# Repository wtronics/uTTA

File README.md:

# uTTA — The Micro ($\mu$) Thermal Transient Analyzer

## What's this TTA stuff anyhow?

Thermal Transient Analysis (TTA) is an advanced technique used to determine the thermal impedance model of a cooling path by measuring its thermal step response. This method is rigorously specified in the **JESD 51-14** standard and is brilliantly summarized in the following tutorials:
* [Transient thermal measurements and thermal equivalent circuit models](https://www.infineon.com/dgdl/Infineon-Thermal_equivalent_circuit_models-ApplicationNotes-v01_02-EN.pdf?fileId=db3a30431a5c32f2011aa65358394dd2) *(Highly recommended!)*
* [Structure function based evaluation of the thermal behavior of an LED](https://repository.tugraz.at/publications/1bz3b-q3w35) *(Definitely worth to read)*

Ideally, after completing a measurement, you should be able to transform the raw captured data into a thermal impedance ($Z_{th}$) curve—a staple graph found in almost every power semiconductor datasheet. In a nutshell, a $Z_{th}$ curve allows engineers to read the specific thermal resistance encountered by a device when a rectangular power pulse of a given duration $x$ is applied. By combining this thermal resistance with the dissipated power, you can calculate the exact junction temperature of the semiconductor at the end of that pulse. 

However, this math only holds true as long as the power pulse is brief enough not to hit the physical thermal boundaries of the semiconductor package itself. Once the heat propagates past those boundaries and into the rest of the assembly, you need a dedicated thermal impedance curve tailored to your specific, real-world cooling path. Nexperia published an excellent application note diving deeper into this topic: 
* [Nexperia AN11156](https://assets.nexperia.com/documents/application-note/AN11156.pdf)

Things get significantly more complicated when dealing with non-rectangular power pulses. While an "extended rectangular" approximation works for a rough estimate, it demands a massive amount of manual effort. Furthermore, if your ultimate goal is running a dynamic thermal simulation, static datasheet graphs are practically useless. For simulation purposes, the most elegant approach is to model the thermal cooling path using a network of RC circuits that mimic the system's heating and cooling behavior. Again, Nexperia offers a fantastic guide on how this is done: 
* [Nexperia AN11261](https://assets.nexperia.com/documents/application-note/AN11261.pdf)

But how do you actually extract these RC models for a specific power semiconductor combined with a custom heatsink? This is where the real headache begins. While you might occasionally find thermal models for a MOSFET, they are almost exclusively provided as encrypted SPICE models. Nexperia is one of the few refreshing exceptions, sometimes offering open thermal equivalent RC networks (structured as either Foster or Cauer models). But when it comes to the heatsink, manufacturers typically provide nothing more than a single, static thermal resistance value.

---

## How to perform these measurements?
### The Proper (and Expensive) Way
Capturing high-fidelity thermal transient measurements requires highly specialized hardware. The industry standard system is called **T3Ster**, originally engineered by MicReD (a Hungarian company later acquired by Siemens). 

Unsurprisingly, industrial equipment like this costs an absolute fortune—well into the high 5-to-6-figure Euro range. Because such professional tools are completely inaccessible for hobbyist or educational budgets, I set out to design and build my own miniature alternative.

### My own little Thermal Transient Analyzer (uTTA)
uTTA began as a passion project during the first COVID-19 lockdown. At the time, I was experimenting heavily with various power electronics (mostly MOSFET-based power switches and electronic loads) and kept running into the exact same wall: *How long can I dissipate a specific amount of surge power in this MOSFET before it reaches its critical destructive temperature?*

While several theoretical methods exist to solve this, every single one of them requires you to know the exact thermal impedance curve of your unique mechanical setup.

#### Target Picture
The following checklist outlines the core objectives of this project and what has been successfully accomplished so far:
* [x] **Measurement Hardware:** Design a hardware platform capable of performing single-channel thermal impedance measurements while simultaneously monitoring at least 2 additional channels for future thermal coupling analysis.
* [x] **Postprocessing Software:** Build a software toolkit to process raw measurement data and extract clean thermal impedance ($Z_{th}$) curves.
* [x] **Thermal Coupling:** Add software/hardware support to measure thermal coupling between adjacent semiconductors.
* [x] **Self-Calibration:** Implement software utilities to calibrate the internal measurement hardware.
* [ ] **Time Constant Spectra:** Implement the ability to calculate the time constant spectrum of the $Z_{th}$ curve via the NID (Network Identification by Deconvolution) method (utilizing either classical FFT deconvolution or a Bayesian approach).
* [ ] **RC Model Extraction:** Automatically extract equivalent RC thermal networks directly from the calculated time constant spectrum.
* [x] **Junction Calibration:** Develop software and hardware tools to calibrate the temperature coefficient of the junction under test.
* [ ] **Hardware Simulator:** Build a dedicated hardware simulator capable of generating highly predictable and repeatable cooling curves to rigorously validate all subsequent software processing steps.

#### Design Requirements
The device must adhere to the following constraints:
* **User-Friendly:** It should be straightforward and intuitive to operate.
* **Cost-Effective:** Extremely cheap and easy to replicate. Target budget: **€150** covering all components and the PCB.
* **Highly Available:** Rely exclusively on off-the-shelf components; absolutely no hard-to-find or "unobtanium" parts.
* **High-Current Handling:** Integrate an onboard heating current switch rated for up to 15A DC which could be upgraded to even higher heating currents.
* **Auxiliary Sensing:** Include a few Type-K thermocouple interfaces for low-speed ambient/heatsink monitoring (< 5 Samples/s).
* **Multi-Junction Tracking:** Capable of measuring the primary Junction Under Test (JUT) alongside 2 secondary monitoring junctions to evaluate thermal coupling.
* **Dynamic Range Optimization:** Provide software-selectable gain settings for the JUT monitor to maximize ADC resolution throughout the transient event.
* **High-Speed Sampling Speed:** Deliver an ultra-fast sampling rate of at least 1MS/s immediately following the deactivation of the heating current to capture the critical early transient behavior.
* **Intelligent Data Reduction:** Automatically taper down the sampling rate as the transient slows down, preventing the accumulation of massive, redundant data logs.
* **Onboard Storage:** Buffer all high-speed data directly to built-in local memory.
* **PC Control:** Managed entirely via a clean, accessible PC graphical user interface (GUI).

---

# The Implementation

## µTTA Hardware
This is the current physical state of the µTTA hardware. The architecture utilizes a compact 3-layer PCB stack enclosed in a custom 3D-printed housing. The design files for the mechanical housing are available under `010_Hardware/060_Mechanics`.

## The Final Test Setup (Simplified)
Below is an overview of the active test setup. The JUT assembly is positioned right next to the power supply. 

> **Note on Environment:** In a professional testing environment, the JUT assembly must be enclosed in a "still air chamber" to isolate the measurement from volatile ambient drafts. Ideally, the device would be mounted onto a temperature-controlled cold plate, but that represents an unnecessary layer of complexity for the scope of this hobby project.

The system is composed of the following core blocks:

### The Heating Power Supply
This unit drives the raw heating current through the Junction Under Test (JUT). While I happen to use a massive 40A bench supply in my lab, any standard power supply featuring an adjustable current limit up to 10A is perfectly adequate for most scenarios. 

The exact current required depends heavily on the specific junction properties and the thermal resistance of the cooling assembly under evaluation. If you are targeting a high-power device with ultra-low thermal resistance (e.g., < 10 K/W), a meatier power supply becomes necessary to force a measurable temperature delta. The supply voltage itself is uncritical; in my configurations, I typically set it to roughly 3V, which provides plenty of headroom to comfortably drive the required current.

### The Junction Under Test
*(To be continued...)*

---

## The JUT Setup

Lacking access to a formal industrial application board I can show in public, I assembled a custom test fixture that closely mimics real-world conditions. The setup consists of three spare MOSFETs bolted to a shared aluminum heatsink. 
The transistors are electrically isolated from the heatsink using standard mica ("glimmer") washers and silicone thermal pads. However, to establish a shared return path for the sense current across all monitored devices, the isolating washers on the mounting screws were intentionally omitted to bridge the drains of all three MOSFETs together. The Gate and Source pins of each individual MOSFET are shorted to prevent spurious turn-on events triggered by static charges. 
Furthermore, each MOSFET is routed through a dedicated coaxial sense cable to accurately monitor the forward voltage drop of the internal body diodes and supply the delicate measurement current. The primary heated junction is also hooked up to heavy-gauge wires to carry the high heating current. These low-inductance lines are custom-made by braiding high-frequency (HF) litz wire. To minimize the overall loop area and shield against inductive voltage spikes, the positive and negative current paths are tightly bundled inside a braided insulating sleeve.

# ToDo
- [x] Build calibration GUI for uTTA hardware.
- [x] Build calibration GUI for DUT scaling factors.
- [x] Document ST Nucleo-Board jumper configurations.
- [ ] Get the mathematical deconvolution algorithm fully operational.
- [ ] Implement automatic RC-model calculation from the time constant spectrum.
- [ ] Develop a modern, native standalone GUI (moving away from LabVIEW).
- [ ] Overhaul and expand the general documentation.

# Possible Improvements for Future Designs
- [ ] Implement finer gain steps for low-level diode voltage measurements.
- [x] Integrate software-controlled offset adjustment via an onboard DAC.
- [x] Integrate software-adjustable measurement current sources (e.g., DAC-controlled Enhanced Howland Current Sources).
- [ ] Migrate away from the ST Nucleo breakout ecosystem in favor of a fully custom, integrated PCB design. *(Benefits: Eliminates bulky stack-up connectors, drastically improves high-speed signal integrity, allows a highly stable dedicated ADC voltage reference, and enables a native onboard USB interface bypassing the ST-Link debugger).*

## Design Choices

Let's be candid: this system is far from a flawless commercial product. As stated at the beginning, this started as a quick-and-dirty quarantine project during the COVID-19 pandemic. I never anticipated that I would still be actively evolving it over 6 years later. The subject matter completely hooked me, though personal commitments have limited the amount of focused time I can dedicate to it. Because both the hardware and software architectures have undergone iterative overhauls, some design choices might appear slightly unorthodox to an outside observer. Here is the underlying engineering rationale:

* **Why store measurement data in local flash memory instead of streaming it directly to a PC over a serial interface?**
  * Our serial connection maxes out at 250 kBaud, which is fundamentally incapable of sustaining the throughput required during the initial 1 MS/s ultra-fast sampling window. Additionally, the microcontroller lacks the RAM capacity required to buffer the millions of high-speed points simultaneously before a delayed dump. Therefore, high-speed hardware-level buffering to external non-volatile storage was mandatory. While I initially used a micro SD card running FATfs, the aggressive write cycles quickly destroyed the cards. Upgrading to a robust NOR Flash chip running **littleFS** completely solved this reliability bottleneck.

* **Why is there only one switchable amplifier? Shouldn't every tracking channel have its own dynamic gain stage?**
  * The switchable programmable gain amplifier (PGA) is intentionally reserved for the primary heated channel. When the massive heating current passes through the JUT, its forward voltage is substantially larger due to the internal resistance. The amplifier must dynamically drop its gain down during this phase to prevent clipping and keep the signal within the measurable ADC window. 
  * The secondary channels, by contrast, are strictly passive—they monitor adjacent unheated diodes utilizing a constant, low-level measurement current where no severe voltage swings occur. A fixed gain stage is perfectly sufficient to map standard silicon diodes or MOSFET body diodes across these monitoring channels.

* **Why did you build the original GUI in LabVIEW?**
  * Frankly, because I use it daily in my day job as a self-proclaimed "lazy" senior hardware developer! 😉 In industrial prototyping, test software needs to be deployed rapidly, and that is precisely where LabVIEW excels. 
  * I am well aware that LabVIEW is quite polarizing in the developer community, but for whipping together a functional, interactive GUI without getting bogged down in TKinter or basic UI positioning math, it remains an incredibly fast tool.
  * **Update (July 1, 2026):** The complete postprocessing toolchain has now been successfully migrated to a modern Python ecosystem utilizing `TTKbootstrap`. Consequently, I am officially working on sunsetting the legacy LabVIEW GUI in upcoming releases. The foundational groundwork was recently completed following the development of our native SCPI driver for the uTTA hardware.

* **Why power the gate driver of the high-current heating switch with an external battery instead of a standard bench supply?**
  * In the early prototyping phases, I did use a secondary isolated bench supply to power the gate drive circuitry. However, I found myself locked in an endless, frustrating battle with nasty common-mode noise issues during high-current switching events. Swapping that power rail over to a completely floating 9V/12V battery completely severed the noise path and instantly wiped out all common-mode artifacts.

---

# A Note on AI

Given how pervasive AI has become in modern software development, I wanted to include a brief, transparent disclosure regarding its role in this repository. This project leverages generative AI to accelerate development velocities and explore alternative conceptual approaches. 

To be clear: the core firmware running on the microcontroller is entirely handwritten from scratch. On the host PC side, things are a bit more collaborative. I heavily utilize AI to spin up structural boilerplate, generate templates, and prototype abstract UI concepts. For instance, the clean HTML layout used to compile the final measurement reports was largely authored by AI, as LLMs are remarkably proficient at building attractive front-end layouts. 

That being said, every single line of code or structural layout spat out by an AI is meticulously peer-reviewed by a human before merging. AI tools are notoriously confident when generating bugs; for example, LLMs absolutely love using deprecated syntax or obsolete methods from older versions of `tkinter` and `TTKbootstrap`. Treat it as a highly capable but slightly reckless assistant!

P.S.: This reame was also redacted by AI :).

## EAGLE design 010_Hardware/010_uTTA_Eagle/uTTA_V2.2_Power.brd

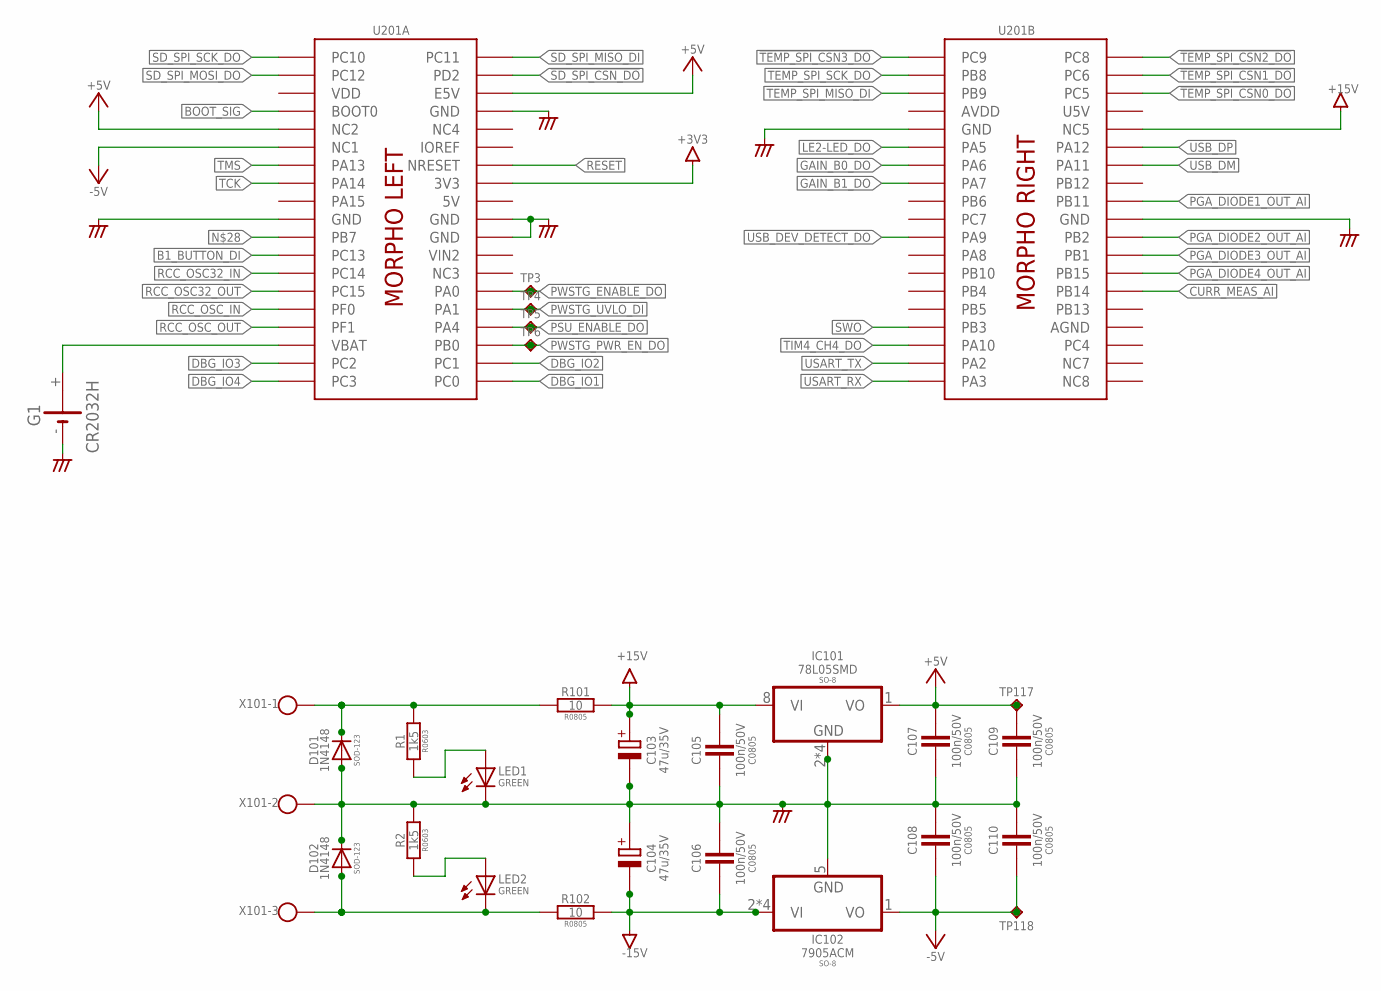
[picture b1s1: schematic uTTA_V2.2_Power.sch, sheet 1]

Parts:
C103, C104: 47u/35V; PANASONIC_D
C105, C106, C107, C108, C109, C110: 100n/50V; C0805
D101, D102: 1N4148; SOD123
G1: CR2032H
IC101: 78L05SMD; SO08
IC102: 7905ACM; SO08
LED1, LED2: GREEN; SML0805
R1, R2: 1k5; R0603
R101, R102: 10; R0805
TP3, TP4, TP5, TP6, TP117, TP118: TPC90H30; C90H30
U201: NUCLEO_F103_BOT; NUCLEO_BRD64_LOWER
X101: AST_03_3,5MM; AST_453_3,5

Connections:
5V: U201.L_5V (5V)
!SD_SPI_CSN_DO: U201.L_PD2 (PD2)
!TEMP_SPI_CSN0_DO: U201.R_PC5 (PC5)
!TEMP_SPI_CSN1_DO: U201.R_PC6 (PC6)
!TEMP_SPI_CSN2_DO: U201.R_PC8 (PC8)
!TEMP_SPI_CSN3_DO: U201.R_PC9 (PC9)
+3V3: U201.L_3V3 (3V3)
+5V: C107.1, C109.1, IC101.1 (VO), TP117.P$1, U201.L_E5V (E5V), U201.L_NC2 (NC2); also elsewhere on the board
+15V: C103.+, C105.1, IC101.8 (VI), R101.2, U201.R_NC5 (NC5)
-5V: C108.2, C110.2, IC102.1 (VO), TP118.P$1, U201.L_NC1 (NC1); also elsewhere on the board
-15V: C104.-, C106.2, IC102.2 (VI), IC102.3 (VI), IC102.6 (VI), IC102.7 (VI), R102.2
AGND: C103.-, C104.+, C105.2, C106.1, C107.2, C108.1, C109.2, C110.1, D101.A, D102.C, G1.-, IC101.2 (GND), IC101.3 (GND), IC101.6 (GND), IC101.7 (GND), IC102.5 (GND), LED1.C, R2.1, U201.L_GND (GND), U201.L_GND3 (GND), U201.L_GND4 (GND), U201.L_GND5 (GND), U201.R_AGND (AGND), U201.R_GND7 (GND), U201.R_GND8 (GND), X101.2_1, X101.2_2; also elsewhere on the board
AVDD: U201.R_AVDD (AVDD)
B1_BUTTON_DI: U201.L_PC13 (PC13)
BOOT_SIG: U201.L_BOOT0 (BOOT0)
CURR_MEAS_AI: U201.R_PB14 (PB14); also elsewhere on the board
DBG_IO1: U201.L_PC0 (PC0)
DBG_IO2: U201.L_PC1 (PC1)
DBG_IO3: U201.L_PC2 (PC2)
DBG_IO4: U201.L_PC3 (PC3)
GAIN_B0_DO: U201.R_PA6 (PA6)
GAIN_B1_DO: U201.R_PA7 (PA7)
IN+: D101.C, R1.1, R101.1, X101.1_1, X101.1_2
IN-: D102.A, LED2.C, R102.1, X101.3_1, X101.3_2
LE2-LED_DO: U201.R_PA5 (PA5)
unnamed: G1.+, U201.L_VBAT (VBAT)
unnamed: LED1.A, R1.2
unnamed: LED2.A, R2.2
PGA_DIODE1_OUT_AI: U201.R_PB11 (PB11)
PGA_DIODE2_OUT_AI: U201.R_PB2 (PB2)
PGA_DIODE3_OUT_AI: U201.R_PB1 (PB1)
PGA_DIODE4_OUT_AI: U201.R_PB15 (PB15)
PSU_ENABLE_DO: TP5.P$1, U201.L_PA4 (PA4); also elsewhere on the board
PWSTG_ENABLE_DO: TP3.P$1, U201.L_PA0 (PA0); also elsewhere on the board
PWSTG_PWR_EN_DO: TP6.P$1, U201.L_PB0 (PB0); also elsewhere on the board
PWSTG_UVLO_DI: TP4.P$1, U201.L_PA1 (PA1); also elsewhere on the board
RCC_OSC32_IN: U201.L_PC14 (PC14)
RCC_OSC32_OUT: U201.L_PC15 (PC15)
RCC_OSC_IN: U201.L_PF0 (PF0)
RCC_OSC_OUT: U201.L_PF1 (PF1)
RESET: U201.L_RESET (NRESET)
SD_SPI_MISO_DI: U201.L_PC11 (PC11)
SD_SPI_MOSI_DO: U201.L_PC12 (PC12)
SD_SPI_SCK_DO: U201.L_PC10 (PC10)
SWO: U201.R_PB3 (PB3)
TCK: U201.L_PA14 (PA14)
TEMP_SPI_MISO_DI: U201.R_PB9 (PB9)
TEMP_SPI_SCK_DO: U201.R_PB8 (PB8)
TIM4_CH4_DO: U201.R_PA10 (PA10)
TMS: U201.L_PA13 (PA13)
U5V: U201.R_U5V (U5V)
USART_RX: U201.R_PA3 (PA3)
USART_TX: U201.R_PA2 (PA2)
USB_DEV_DETECT_DO: U201.R_PA9 (PA9)
USB_DM: U201.R_PA11 (PA11)
USB_DP: U201.R_PA12 (PA12)
VDD: U201.L_VDD (VDD)
VIN2: U201.L_VIN (VIN2)

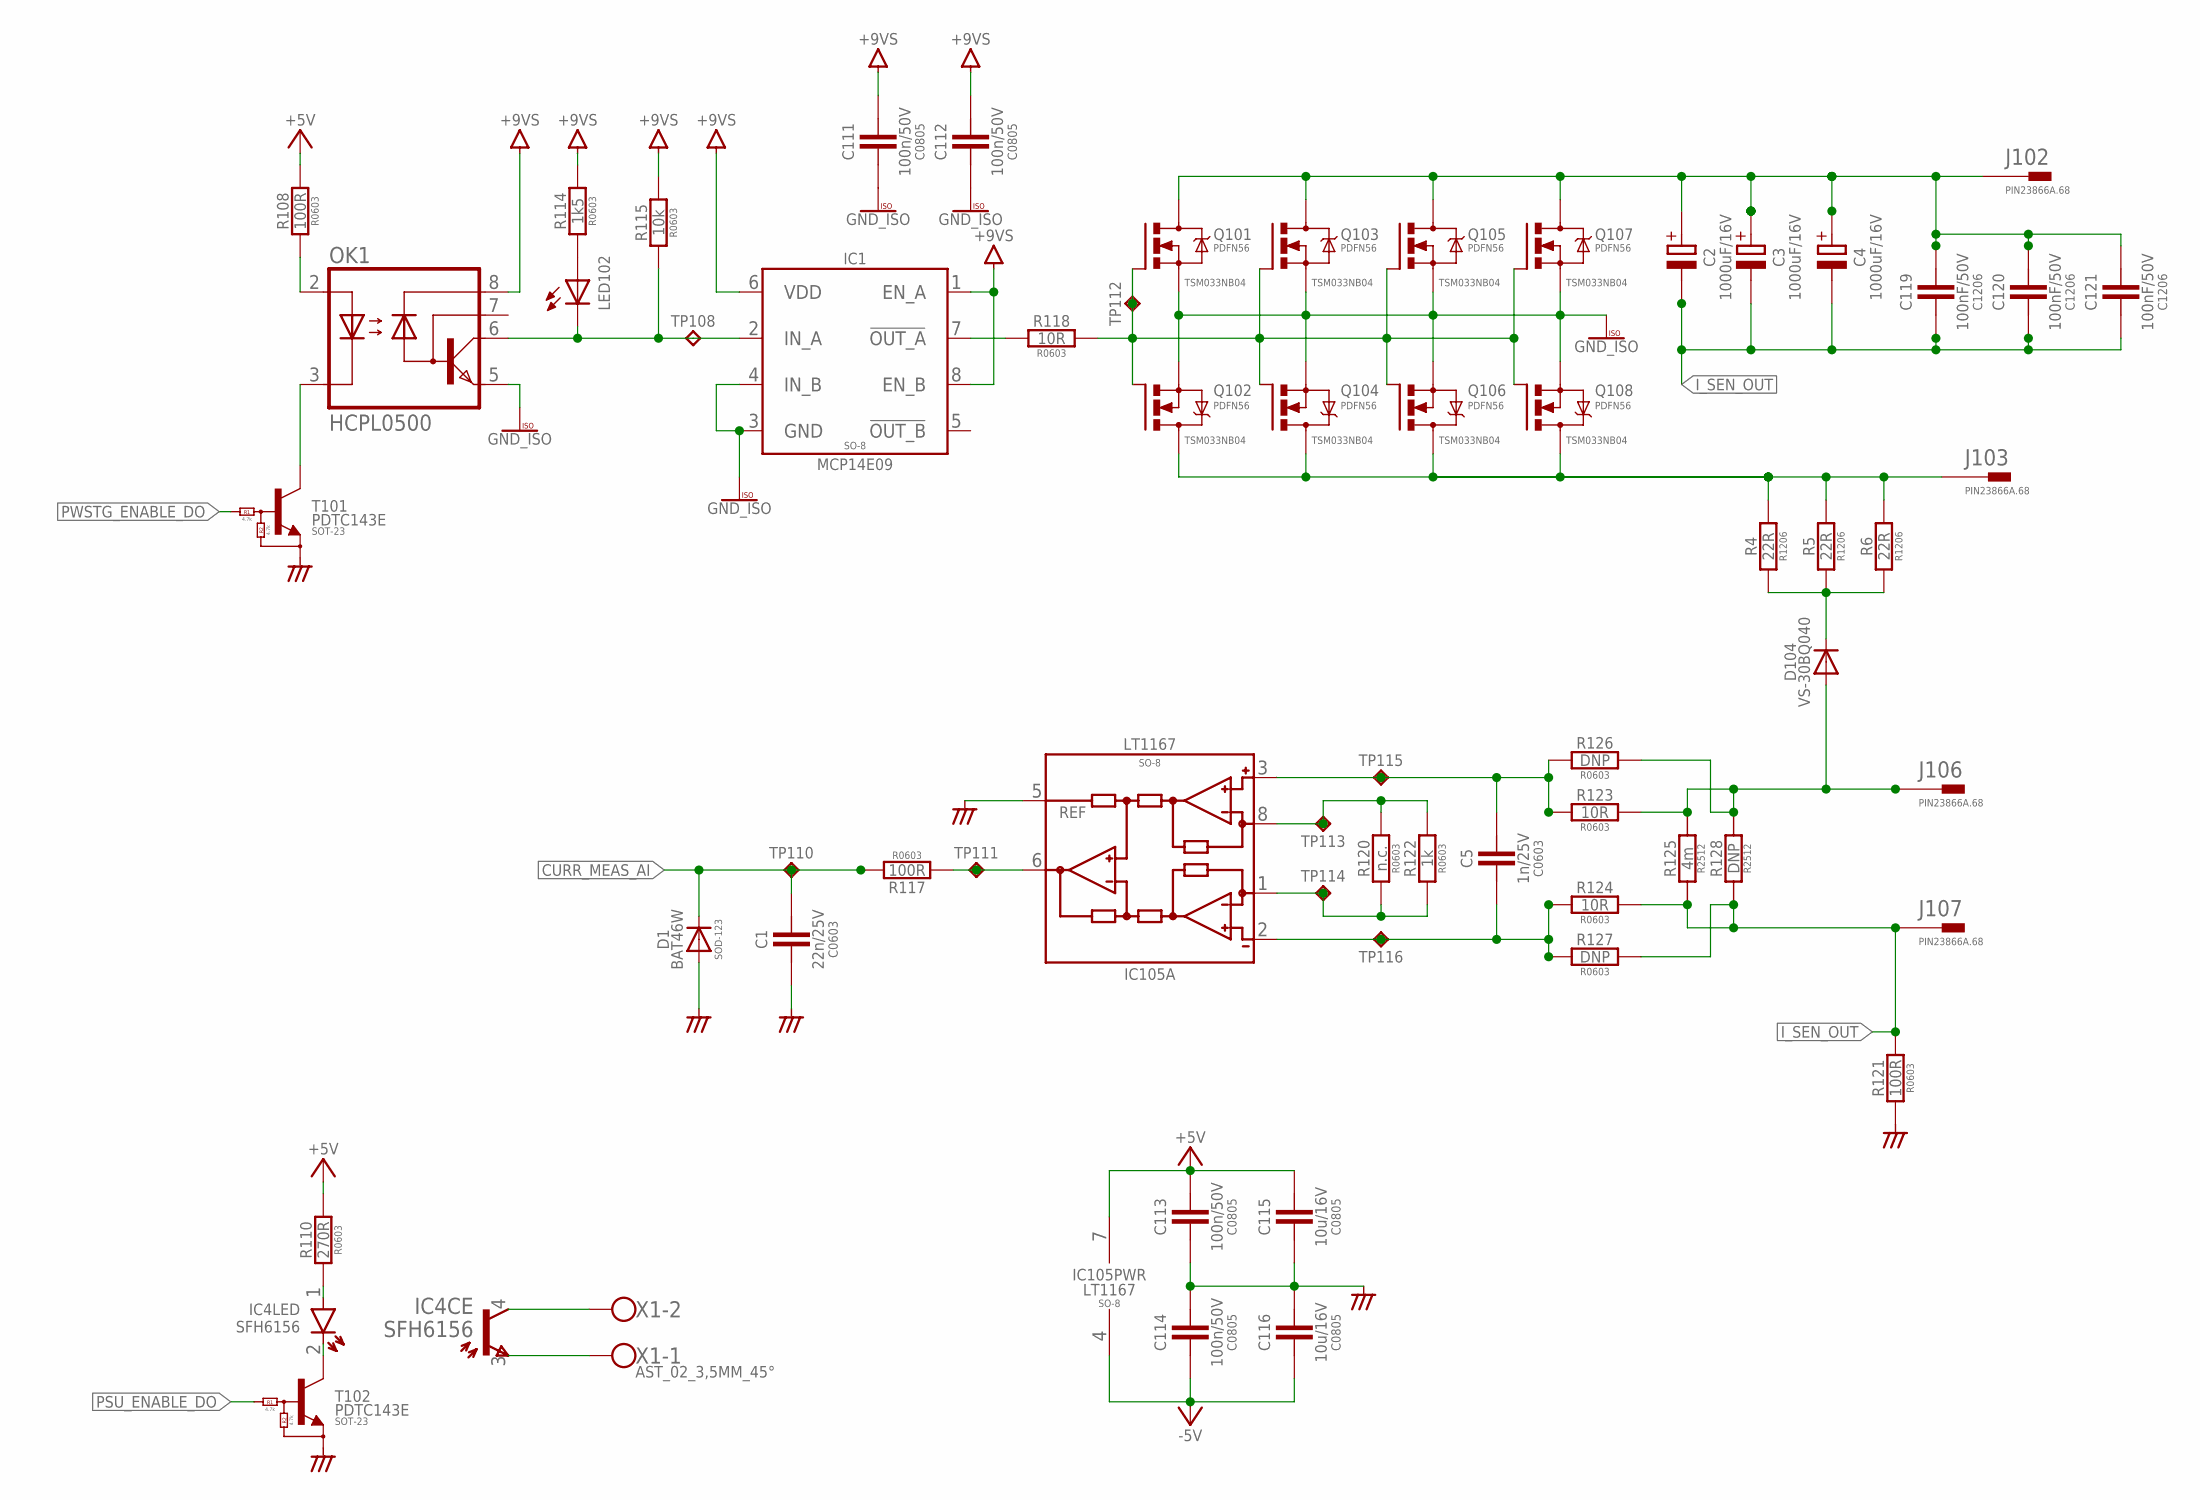
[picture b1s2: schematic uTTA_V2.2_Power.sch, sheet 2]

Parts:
C1: 22n/25V; C0603
C2, C3, C4: 1000uF/16V; E5-10,5
C5: 1n/25V; C0603
C111, C112, C113, C114: 100n/50V; C0805
C115, C116: 10u/16V; C0805
C119, C120, C121: 100nF/50V; C1206
D1: BAT46W; SOD123
D104: VS-30BQ040; SMC
IC1: MCP14E09; SO-08
IC4: SFH6156; SFH; MPN SFH6156-4T
IC105: LT1167; SO08
J102, J103, J106, J107: PIN23866A.68; VOGT_3866A.68
LED102: LEDSML0805; SML0805
OK1: HCPL0500; SOIC08
Q101, Q102, Q103, Q104, Q105, Q106, Q107, Q108: TSM033NB04; PDFN56
R4, R5, R6: 22R; R1206
R108, R117, R121: 100R; R0603
R110: 270R; R0603
R114: 1k5; R0603
R115: 10k; R0603
R118, R123, R124: 10R; R0603
R120: n.c.; R0603
R122: 1k; R0603
R125: 4m; R2512
R126, R127: DNP; R0603
R128: DNP; R2512
T101, T102: PDTC143E; SOT23
TP108, TP110, TP111, TP112, TP115, TP116: TPC90H30; C90H30
TP113, TP114: TP; C90
X1: AST_02_3,5MM_45°; AST_452_3,5

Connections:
9V_SWITCHED: C111.1, C112.1, IC1.1 (EN_A), IC1.6 (VDD), IC1.8 (EN_B), OK1.8 (VCC), R114.1, R115.1; also elsewhere on the board
+5V: C113.1, C115.1, IC105.7 (V+), R108.1, R110.1; also elsewhere on the board
-5V: C114.2, C116.2, IC105.4 (V-); also elsewhere on the board
AGND: C1.2, C113.2, C114.1, C115.2, C116.1, D1.A, IC105.5 (REF), R121.1, T101.2 (E), T102.2 (E); also elsewhere on the board
CURR_AMP_GAIN_N: IC105.1 (RG), R120.1, R122.1, TP114.P$1
CURR_AMP_GAIN_P: IC105.8 (RG), R120.2, R122.2, TP113.P$1
CURR_AMP_OUT: IC105.6 (OUT), R117.2, TP111.P$1
CURR_MEAS_AI: C1.1, D1.C, R117.1, TP110.P$1; also elsewhere on the board
GND_ISO: C111.2, C112.2, IC1.3 (GND), IC1.4 (IN_B), OK1.5 (GND), Q101.P$1 (S), Q101.P$2 (S), Q101.P$3 (S), Q102.P$1 (S), Q102.P$2 (S), Q102.P$3 (S), Q103.P$1 (S), Q103.P$2 (S), Q103.P$3 (S), Q104.P$1 (S), Q104.P$2 (S), Q104.P$3 (S), Q105.P$1 (S), Q105.P$2 (S), Q105.P$3 (S), Q106.P$1 (S), Q106.P$2 (S), Q106.P$3 (S), Q107.P$1 (S), Q107.P$2 (S), Q107.P$3 (S), Q108.P$1 (S), Q108.P$2 (S), Q108.P$3 (S); also elsewhere on the board
I_SENSE_N: C5.2, IC105.2 (-IN), R124.2, R127.2, TP116.P$1
I_SENSE_P: C5.1, IC105.3 (+IN), R123.1, R126.1, TP115.P$1
I_SEN_IN: D104.A, J106.A1, J106.A2, R123.2, R125.2 (B), R126.2, R128.2 (B)
I_SEN_OUT: C2.-, C3.-, C4.-, C119.2, C120.2, C121.2, J107.A1, J107.A2, R121.2, R124.1, R125.1 (A), R127.1, R128.1 (A)
unnamed: C2.+, C3.+, C4.+, C119.1, C120.1, C121.1, J102.A1, J102.A2, Q101.P$5 (D), Q101.P$6 (D), Q101.P$7 (D), Q101.P$8 (D), Q101.P$9 (D), Q103.P$5 (D), Q103.P$6 (D), Q103.P$7 (D), Q103.P$8 (D), Q103.P$9 (D), Q105.P$5 (D), Q105.P$6 (D), Q105.P$7 (D), Q105.P$8 (D), Q105.P$9 (D), Q107.P$5 (D), Q107.P$6 (D), Q107.P$7 (D), Q107.P$8 (D), Q107.P$9 (D)
unnamed: IC1.7 (!OUT_A), R118.2
unnamed: Q101.P$4 (G), Q102.P$4 (G), Q103.P$4 (G), Q104.P$4 (G), Q105.P$4 (G), Q106.P$4 (G), Q107.P$4 (G), Q108.P$4 (G), R118.1, TP112.P$1
unnamed: IC4.1 (A), R110.2
unnamed: IC1.2 (IN_A), LED102.C, OK1.6 (VO), R115.2, TP108.P$1
unnamed: IC4.2 (K), T102.3 (C)
unnamed: LED102.A, R114.2
unnamed: OK1.3 (C), T101.3 (C)
unnamed: D104.C, R4.1, R5.1, R6.1
unnamed: OK1.2 (A), R108.2
unnamed: J103.A1, J103.A2, Q102.P$5 (D), Q102.P$6 (D), Q102.P$7 (D), Q102.P$8 (D), Q102.P$9 (D), Q104.P$5 (D), Q104.P$6 (D), Q104.P$7 (D), Q104.P$8 (D), Q104.P$9 (D), Q106.P$5 (D), Q106.P$6 (D), Q106.P$7 (D), Q106.P$8 (D), Q106.P$9 (D), Q108.P$5 (D), Q108.P$6 (D), Q108.P$7 (D), Q108.P$8 (D), Q108.P$9 (D), R4.2, R5.2, R6.2
OK_PSU_C: IC4.4 (C), X1.2_1, X1.2_2
OK_PSU_E: IC4.3 (E), X1.1_1, X1.1_2
PSU_ENABLE_DO: T102.1 (B); also elsewhere on the board
PWSTG_ENABLE_DO: T101.1 (B); also elsewhere on the board

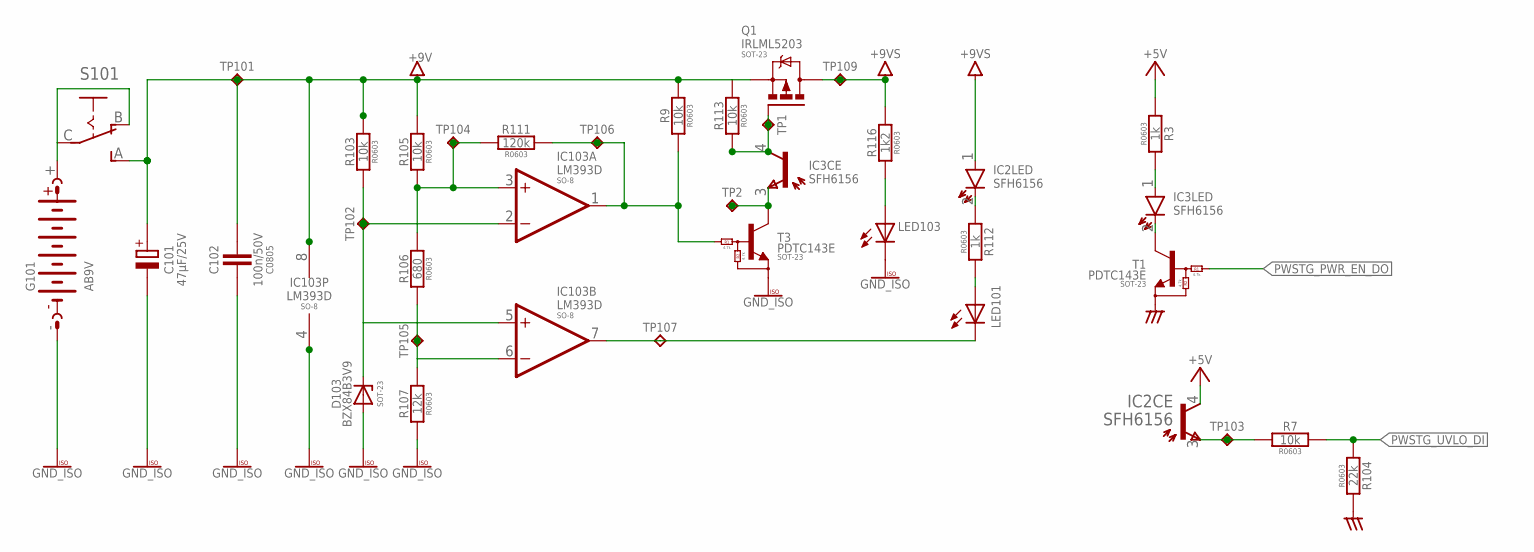
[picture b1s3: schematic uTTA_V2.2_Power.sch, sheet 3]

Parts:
C101: 47µF/25V; PANASONIC_D
C102: 100n/50V; C0805
D103: BZX84B3V9; SOT23
G101: AB9V
IC2, IC3: SFH6156; SFH
IC103: LM393D; SO08
LED101, LED103: LEDSML0805; SML0805
Q1: IRLML5203; MICRO3
R3, R112: 1k; R0603
R7, R9, R103, R105, R113: 10k; R0603
R104: 22k; R0603
R106: 680; R0603
R107: 12k; R0603
R111: 120k; R0603
R116: 1k2; R0603
S101: SS_ESP101
T1, T3: PDTC143E; SOT23
TP1, TP2, TP101, TP102, TP103, TP104, TP105, TP106, TP107, TP109: TPC90H30; C90H30

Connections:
9V_SWITCHED: IC2.1 (A), Q1.3 (D), R116.1, TP109.P$1; also elsewhere on the board
+5V: IC2.4 (C), R3.2; also elsewhere on the board
+9V: C101.+, C102.1, IC103.8 (V+), Q1.2 (S), R9.1, R103.1, R105.1, R113.1, S101.A (S), TP101.P$1
AGND: R104.2, T1.2 (E); also elsewhere on the board
GND_ISO: C101.-, C102.2, D103.1 (A), G101.-, IC103.4 (V-), LED103.C, R107.2, T3.2 (E); also elsewhere on the board
unnamed: IC103.7 (OUT), LED101.C, TP107.P$1
unnamed: G101.+, S101.B (O), S101.C
unnamed: LED103.A, R116.2
unnamed: IC3.4 (C), Q1.1 (G), R113.2, TP1.P$1
unnamed: IC3.2 (K), T1.3 (C)
unnamed: IC3.1 (A), R3.1
unnamed: IC2.3 (E), R7.1, TP103.P$1
unnamed: IC3.3 (E), T3.3 (C), TP2.P$1
unnamed: D103.3 (C), IC103.2 (-IN), IC103.5 (+IN), R103.2, TP102.P$1
unnamed: IC103.6 (-IN), R106.2, R107.1, TP105.P$1
unnamed: IC103.3 (+IN), R105.2, R106.1, R111.2, TP104.P$1
unnamed: IC2.2 (K), R112.2
unnamed: IC103.1 (OUT), R9.2, R111.1, T3.1 (B), TP106.P$1
unnamed: LED101.A, R112.1
PWSTG_PWR_EN_DO: T1.1 (B); also elsewhere on the board
PWSTG_UVLO_DI: R7.2, R104.1; also elsewhere on the board

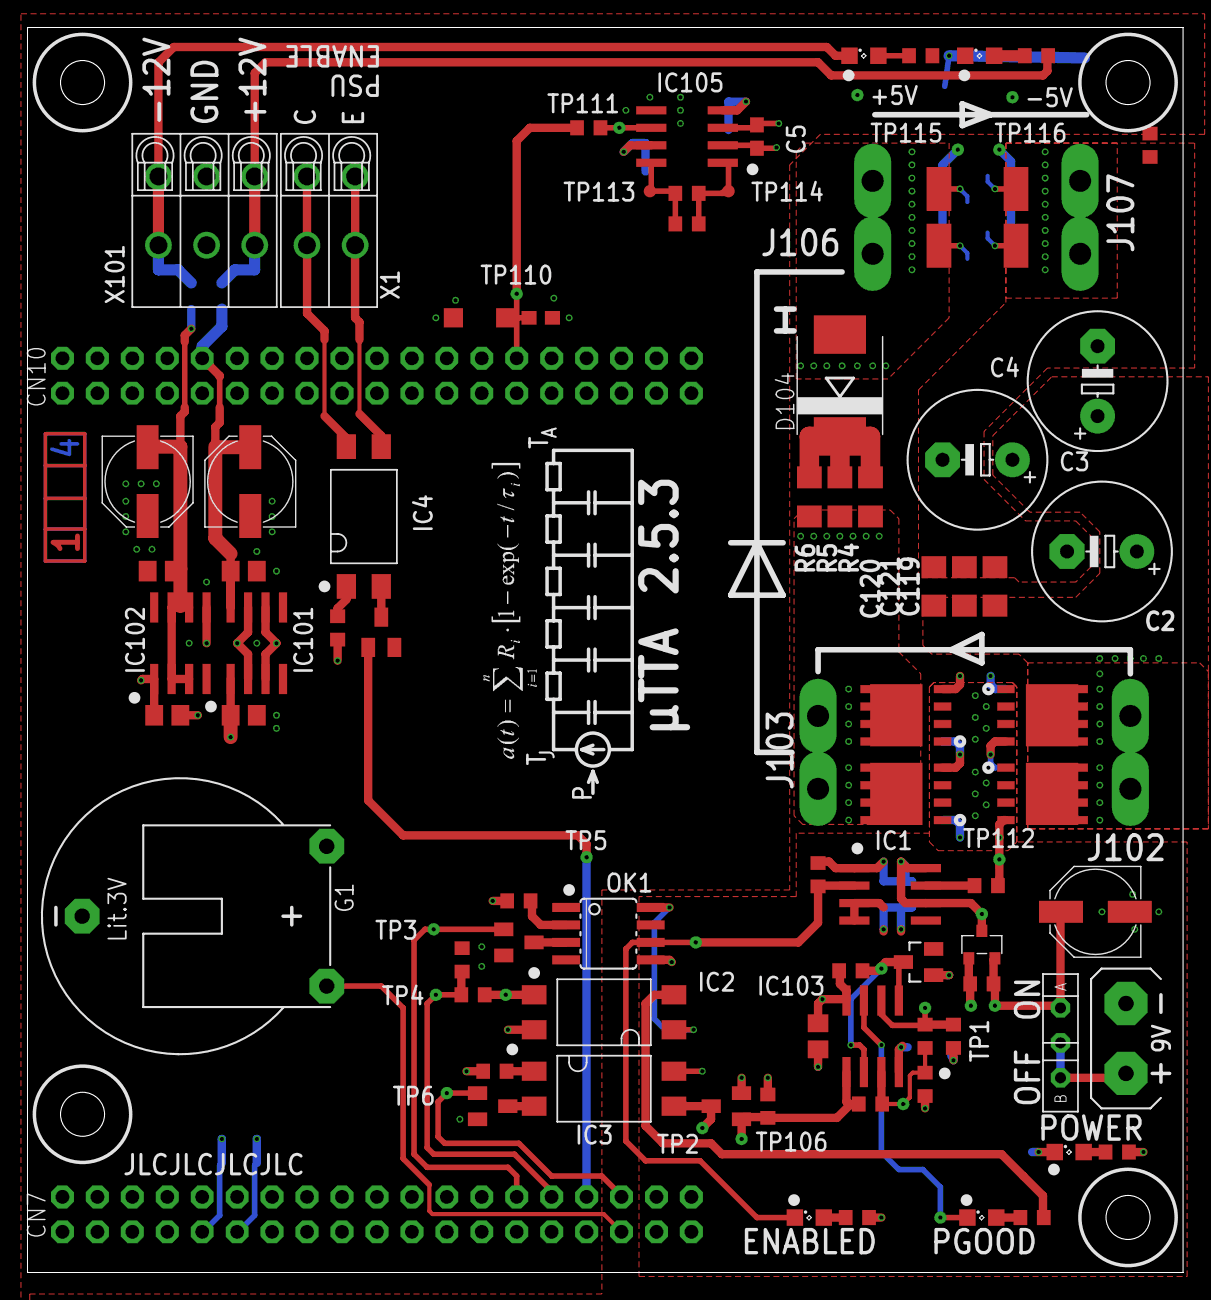
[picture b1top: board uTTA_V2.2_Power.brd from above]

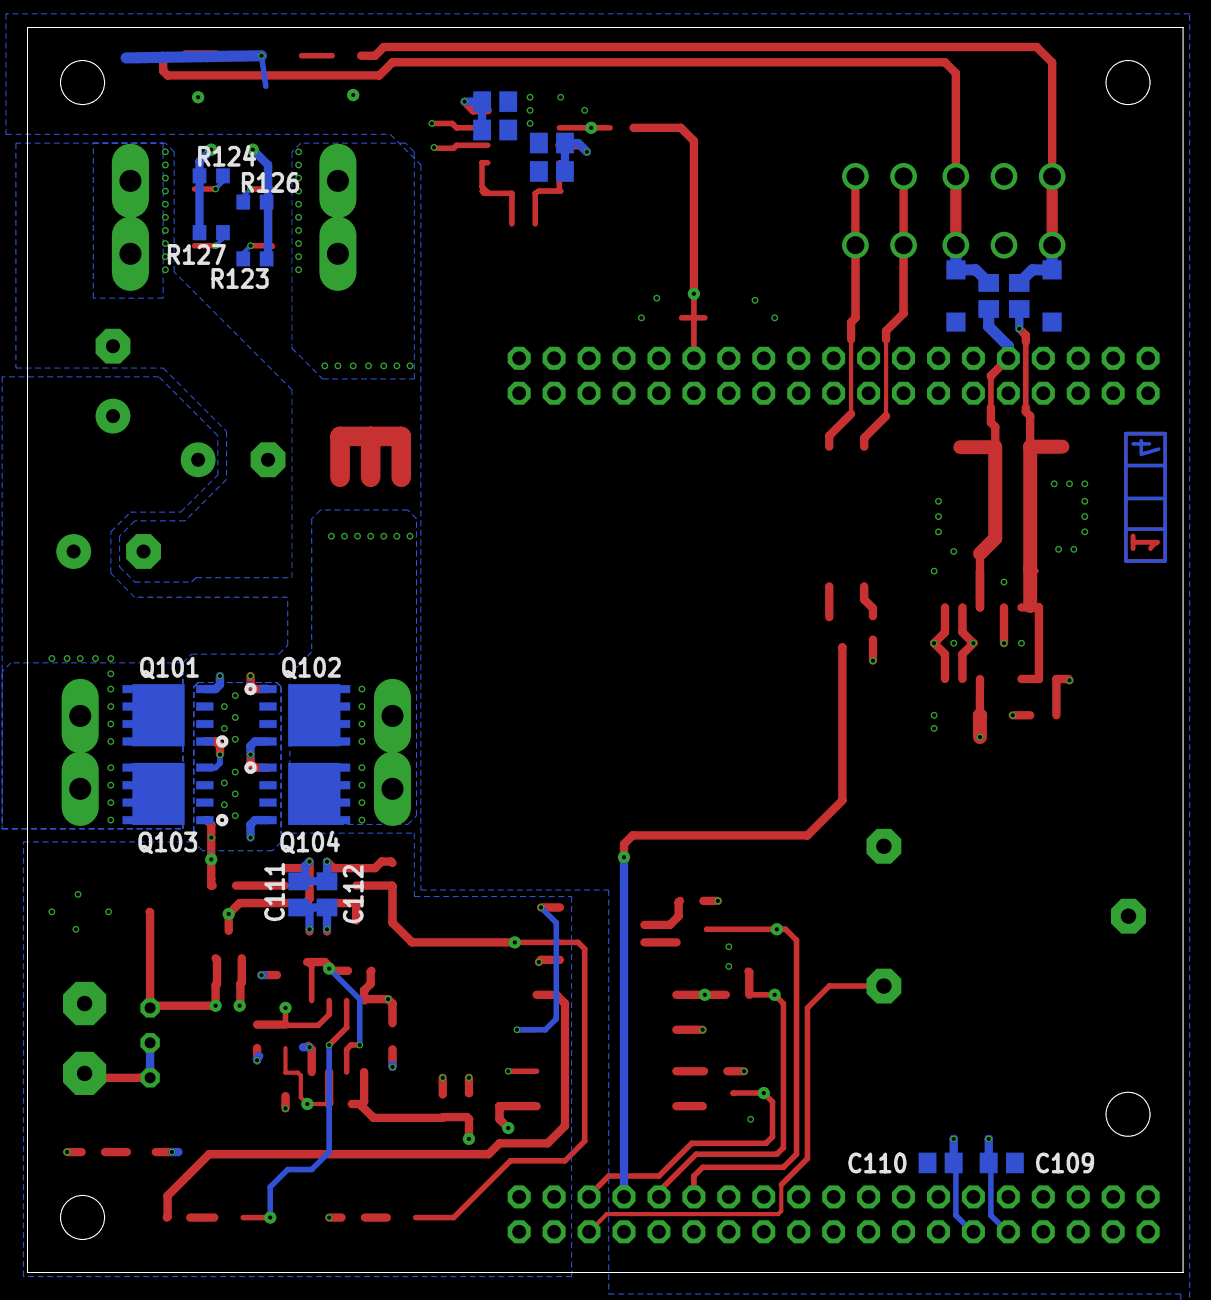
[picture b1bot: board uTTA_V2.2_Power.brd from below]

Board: 4 copper layers, 84.0 x 90.5 mm, 125 parts (20 on the bottom side), 52 nets.

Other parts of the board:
U$7: A4_LOC_CC_BY_NC_SA

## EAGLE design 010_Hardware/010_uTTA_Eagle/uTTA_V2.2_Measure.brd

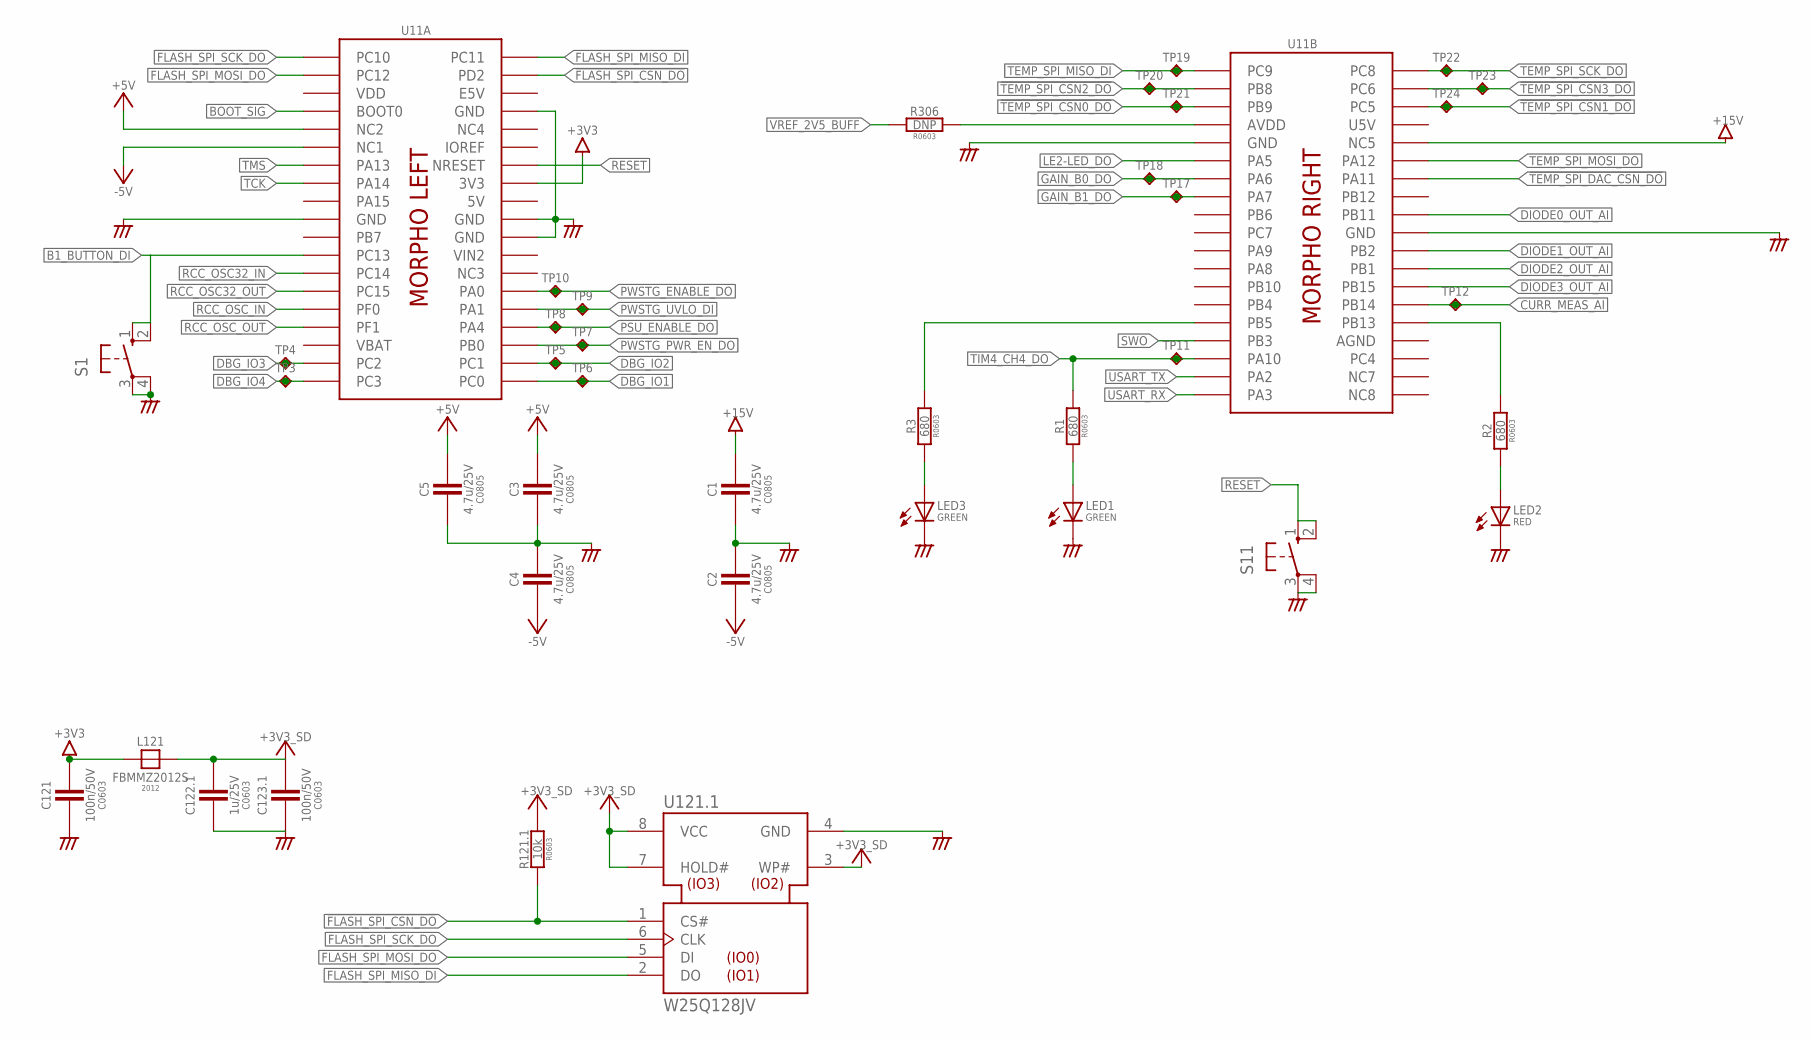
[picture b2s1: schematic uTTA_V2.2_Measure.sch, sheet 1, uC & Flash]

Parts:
C1, C2, C3, C4, C5: 4.7u/25V; C0805
C121, C123.1: 100n/50V; C0603
C122.1: 1u/25V; C0603
L121: FBMMZ2012S; FB2012
LED1, LED3: GREEN; SML0805
LED2: RED; SML0805
R1, R2, R3: 680; R0603
R121.1: 10k; R0603
R306: DNP; R0603
S1: 10-XX; B3F-10XX; MPN B3F-1000
S11: 10-XX; B3F-10XX
TP3, TP4, TP5, TP6, TP7, TP8, TP9, TP10, TP11, TP12, TP17, TP18, TP19, TP20, TP21, TP22, TP23, TP24: TPC90H30; C90H30
U11: NUCLEO_F103_BOT; NUCLEO_BRD64_LOWER
U121.1: W25Q128JV; SO08W

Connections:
5V: U11.L_5V (5V)
!FLASH_SPI_CSN_DO: R121.1.2, U11.L_PD2 (PD2), U121.1.1 (CS#)
!TEMP_SPI_CSN0_DO: TP21.P$1, U11.R_PB9 (PB9); also elsewhere on the board
!TEMP_SPI_CSN1_DO: TP24.P$1, U11.R_PC5 (PC5); also elsewhere on the board
!TEMP_SPI_CSN2_DO: TP20.P$1, U11.R_PB8 (PB8); also elsewhere on the board
!TEMP_SPI_CSN3_DO: TP23.P$1, U11.R_PC6 (PC6); also elsewhere on the board
!TEMP_SPI_DAC_CSN_DO: U11.R_PA11 (PA11); also elsewhere on the board
+3V3: C121.1, L121.1, U11.L_3V3 (3V3); also elsewhere on the board
+5V: C3.1, C5.1, U11.L_NC2 (NC2); also elsewhere on the board
+5V/4: C122.1.1, C123.1.1, L121.2, R121.1.1, U121.1.3 (WP#), U121.1.7 (HOLD#), U121.1.8 (VCC)
+15V: C1.1, U11.R_NC5 (NC5); also elsewhere on the board
-5V: C2.2, C4.2, U11.L_NC1 (NC1); also elsewhere on the board
AGND: C1.2, C2.1, C3.2, C4.1, C5.2, C121.2, C122.1.2, C123.1.2, LED1.C, LED2.C, LED3.C, S1.3, S1.4 (P1), S11.3, S11.4 (P1), U11.L_GND (GND), U11.L_GND3 (GND), U11.L_GND4 (GND), U11.L_GND5 (GND), U11.R_AGND (AGND), U11.R_GND7 (GND), U11.R_GND8 (GND), U121.1.4 (GND); also elsewhere on the board
B1_BUTTON_DI: S1.1 (S), S1.2 (S1), U11.L_PC13 (PC13)
BOOT_SIG: U11.L_BOOT0 (BOOT0)
CURR_MEAS_AI: TP12.P$1, U11.R_PB14 (PB14)
DBG_IO1: TP6.P$1, U11.L_PC0 (PC0)
DBG_IO2: TP5.P$1, U11.L_PC1 (PC1)
DBG_IO3: TP4.P$1, U11.L_PC2 (PC2)
DBG_IO4: TP3.P$1, U11.L_PC3 (PC3)
DIODE0_OUT_AI: U11.R_PB11 (PB11); also elsewhere on the board
DIODE1_OUT_AI: U11.R_PB2 (PB2); also elsewhere on the board
DIODE2_OUT_AI: U11.R_PB1 (PB1); also elsewhere on the board
DIODE3_OUT_AI: U11.R_PB15 (PB15); also elsewhere on the board
E5V: U11.L_E5V (E5V)
FLASH_SPI_MISO_DI: U11.L_PC11 (PC11), U121.1.2 (DO)
FLASH_SPI_MOSI_DO: U11.L_PC12 (PC12), U121.1.5 (DI)
FLASH_SPI_SCK_DO: U11.L_PC10 (PC10), U121.1.6 (CLK)
GAIN_B0_DO: TP18.P$1, U11.R_PA6 (PA6); also elsewhere on the board
GAIN_B1_DO: TP17.P$1, U11.R_PA7 (PA7); also elsewhere on the board
LE2-LED_DO: U11.R_PA5 (PA5)
unnamed: LED2.A, R2.2
unnamed: LED3.A, R3.2
unnamed: LED1.A, R1.2
PSU_ENABLE_DO: TP8.P$1, U11.L_PA4 (PA4)
PWSTG_ENABLE_DO: TP10.P$1, U11.L_PA0 (PA0)
PWSTG_PWR_EN_DO: TP7.P$1, U11.L_PB0 (PB0)
PWSTG_UVLO_DI: TP9.P$1, U11.L_PA1 (PA1)
RCC_OSC32_IN: U11.L_PC14 (PC14)
RCC_OSC32_OUT: U11.L_PC15 (PC15)
RCC_OSC_IN: U11.L_PF0 (PF0)
RCC_OSC_OUT: U11.L_PF1 (PF1)
RESET: S11.1 (S), S11.2 (S1), U11.L_RESET (NRESET)
SWO: U11.R_PB3 (PB3)
TCK: U11.L_PA14 (PA14)
TEMP_SPI_MISO_DI: TP19.P$1, U11.R_PC9 (PC9); also elsewhere on the board
TEMP_SPI_MOSI_DO: U11.R_PA12 (PA12); also elsewhere on the board
TEMP_SPI_SCK_DO: TP22.P$1, U11.R_PC8 (PC8); also elsewhere on the board
TIM4_CH4_DO: R1.1, TP11.P$1, U11.R_PA10 (PA10)
TIM4_CH4_DO1: R2.1, U11.R_PB13 (PB13)
TIM4_CH4_DO2: R3.1, U11.R_PB5 (PB5)
TMS: U11.L_PA13 (PA13)
U5V: U11.R_U5V (U5V)
USART_RX: U11.R_PA3 (PA3)
USART_TX: U11.R_PA2 (PA2)
VBAT: U11.L_VBAT (VBAT)
VDD: U11.L_VDD (VDD)
VIN2: U11.L_VIN (VIN2)
VREF_2V5_ADCREF: R306.2, U11.R_AVDD (AVDD)
VREF_2V5_BUFF: R306.1; also elsewhere on the board

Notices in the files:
020_uC_Software/uTTA/Core/Inc/main.h:
Copyright (c) 2024 STMicroelectronics.
All rights reserved.
This software is licensed under terms that can be found in the LICENSE file
